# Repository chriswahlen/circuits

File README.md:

# Circuits!

This repo will contain any misc circuits I happen to build.

## LMR51430 Power

A 5V 3A power supply, with an input range of 7V - 12V. Can be enabled via
external signal.

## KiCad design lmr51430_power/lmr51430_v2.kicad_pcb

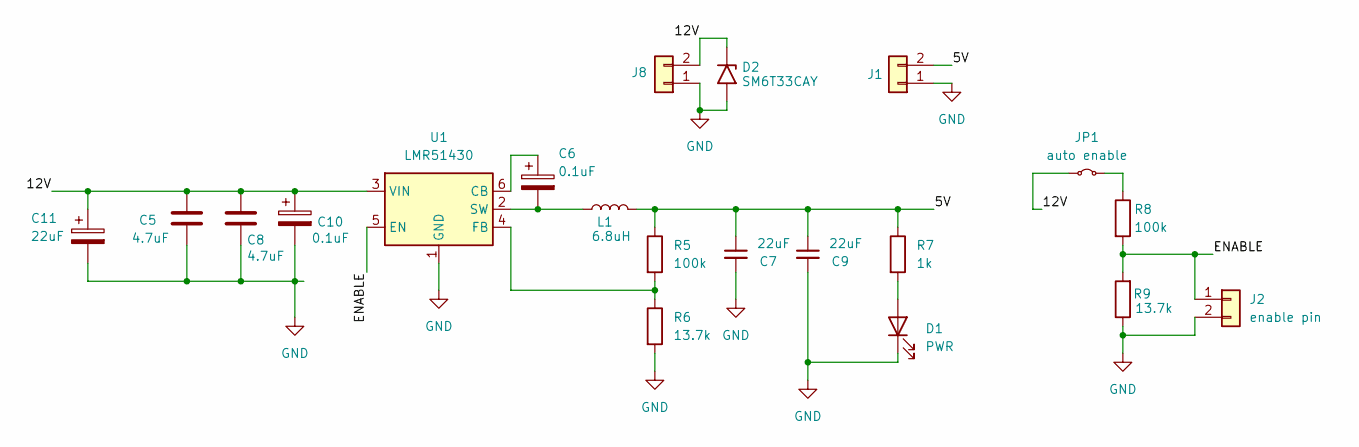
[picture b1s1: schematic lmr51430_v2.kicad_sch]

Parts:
C5, C8: 4.7uF; C_0805_2012Metric_Pad1.18x1.45mm_HandSolder
C6, C10: 0.1uF; C_0805_2012Metric_Pad1.18x1.45mm_HandSolder
C7, C9: 22uF; C_1210_3225Metric_Pad1.33x2.70mm_HandSolder
C11: 22uF; CP_Radial_D5.0mm_P2.00mm
D1: PWR; LED_1206_3216Metric_Pad1.42x1.75mm_HandSolder
D2: SM6T33CAY; D_SMB
J1: GND %V; JST_VH_B2P-VH-B_1x02_P3.96mm_Vertical
J2: enable pin; JST_PH_B2B-PH-K_1x02_P2.00mm_Vertical
J8: IN; JST_VH_B2P-VH-B_1x02_P3.96mm_Vertical
JP1: auto enable; SolderJumper-2_P1.3mm_Bridged_RoundedPad1.0x1.5mm
L1: 6.8uH; L_Taiyo-Yuden_NR-80xx_HandSoldering
R5, R8: 100k; R_0805_2012Metric_Pad1.20x1.40mm_HandSolder
R6, R9: 13.7k; R_0805_2012Metric_Pad1.20x1.40mm_HandSolder
R7: 1k; R_0805_2012Metric_Pad1.20x1.40mm_HandSolder
U1: LMR51430; SOT-23-6

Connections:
/5V: C7.1, C9.1, J1.2, L1.2, R5.1, R7.1
/12V: C5.1, C8.1, C10.1, C11.1, D2.1 (A1), J8.2, JP1.1 (A), U1.3 (VIN)
/ENABLE: J2.1, R8.2, R9.2, U1.5 (EN)
GND: C5.2, C7.2, C8.2, C9.2, C10.2, C11.2, D1.1 (K), D2.2 (A2), J1.1, J2.2, J8.1, R6.2, R9.1, U1.1 (GND)
unnamed: D1.2 (A), R7.2
unnamed: JP1.2 (B), R8.1
unnamed: C6.1, U1.6 (CB)
unnamed: R5.2, R6.1, U1.4 (FB)
unnamed: C6.2, L1.1, U1.2 (SW)

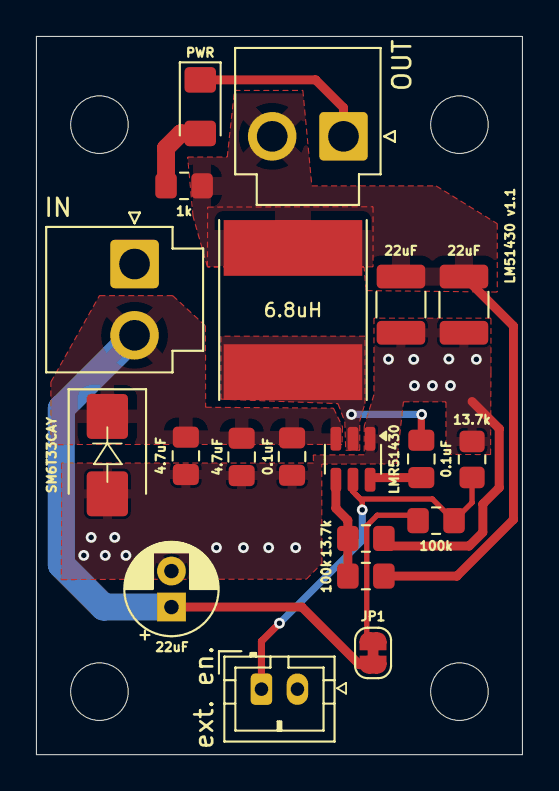
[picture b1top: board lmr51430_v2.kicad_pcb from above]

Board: 2 copper layers, 27.0 x 39.9 mm, 24 parts (0 on the bottom side), 9 nets.

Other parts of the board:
H1, H2, H3, H4: MountingHole_3.2mm_M3

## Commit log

2025-04-15 Add LMR51430 design
